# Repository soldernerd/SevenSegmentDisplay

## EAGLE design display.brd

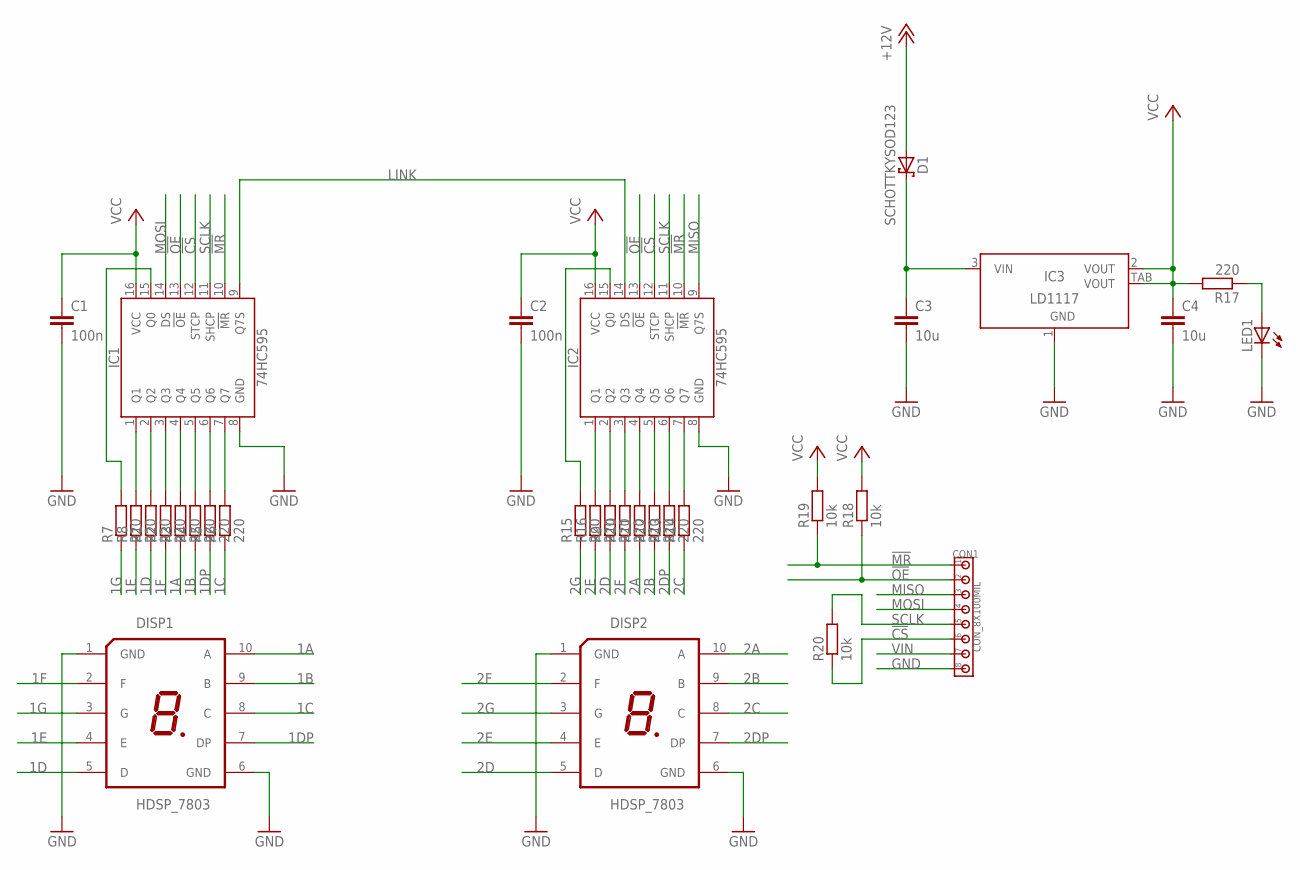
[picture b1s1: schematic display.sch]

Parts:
C1, C2: 100n; C1206
C3, C4: 10u; C1206
CON1: CON_8X100MIL; 100MIL_8X
D1: SCHOTTKYSOD123; SOD123
DISP1, DISP2: HDSP_7803; HDSP-A
IC1, IC2: 74HC595; SO16
IC3: LD1117; SOT223
LED1: LED1206
R1, R2, R3, R4, R5, R6, R7, R8, R9, R10, R11, R12, R13, R14, R15, R16, R17: 220; R1206
R18, R19, R20: 10k; R1206

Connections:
1A: DISP1.10 (A), R3.1
1B: DISP1.9 (B), R4.1
1C: DISP1.8 (C), R6.1
1D: DISP1.5 (D), R1.1
1DP: DISP1.7 (DP), R5.1
1E: DISP1.4 (E), R8.1
1F: DISP1.2 (F), R2.1
1G: DISP1.3 (G), R7.1
2A: DISP2.10 (A), R11.1
2B: DISP2.9 (B), R12.1
2C: DISP2.8 (C), R14.1
2D: DISP2.5 (D), R9.1
2DP: DISP2.7 (DP), R13.1
2E: DISP2.4 (E), R16.1
2F: DISP2.2 (F), R10.1
2G: DISP2.3 (G), R15.1
!CS!: CON1.6, IC1.12 (STCP), IC2.12 (STCP), R20.1
!MR!: CON1.1, IC1.10 (!MR!), IC2.10 (!MR!), R19.1
!OE!: CON1.2, IC1.13 (!OE!), IC2.13 (!OE!), R18.1
GND: C1.2, C2.2, C3.2, C4.2, CON1.8, DISP1.1 (GND), DISP1.6 (GND), DISP2.1 (GND), DISP2.6 (GND), IC1.8 (GND), IC2.8 (GND), IC3.1 (GND), LED1.C
LINK: IC1.9 (Q7S), IC2.14 (DS)
MISO: CON1.3, IC2.9 (Q7S)
MOSI: CON1.4, IC1.14 (DS)
unnamed: IC1.15 (Q0), R7.2
unnamed: IC1.7 (Q7), R6.2
unnamed: IC1.6 (Q6), R5.2
unnamed: IC1.5 (Q5), R4.2
unnamed: IC1.4 (Q4), R3.2
unnamed: IC1.3 (Q3), R2.2
unnamed: IC1.2 (Q2), R1.2
unnamed: IC1.1 (Q1), R8.2
unnamed: IC2.15 (Q0), R15.2
unnamed: IC2.7 (Q7), R14.2
unnamed: IC2.6 (Q6), R13.2
unnamed: IC2.5 (Q5), R12.2
unnamed: IC2.4 (Q4), R11.2
unnamed: IC2.3 (Q3), R10.2
unnamed: IC2.2 (Q2), R9.2
unnamed: IC2.1 (Q1), R16.2
unnamed: C3.1, D1.C, IC3.3 (VIN)
unnamed: LED1.A, R17.1
SCLK: CON1.5, IC1.11 (SHCP), IC2.11 (SHCP), R20.2
VCC: C1.1, C2.1, C4.1, IC1.16 (VCC), IC2.16 (VCC), IC3.2 (VOUT), IC3.TAB (VOUT), R17.2, R18.2, R19.2
VIN: CON1.7, D1.A

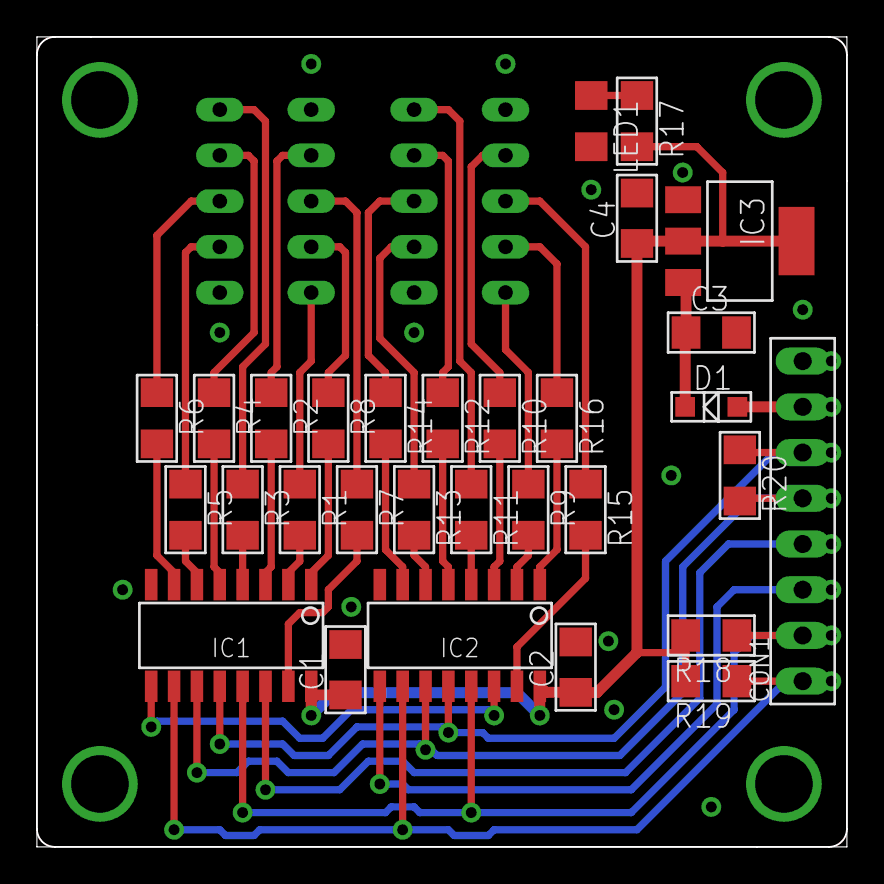
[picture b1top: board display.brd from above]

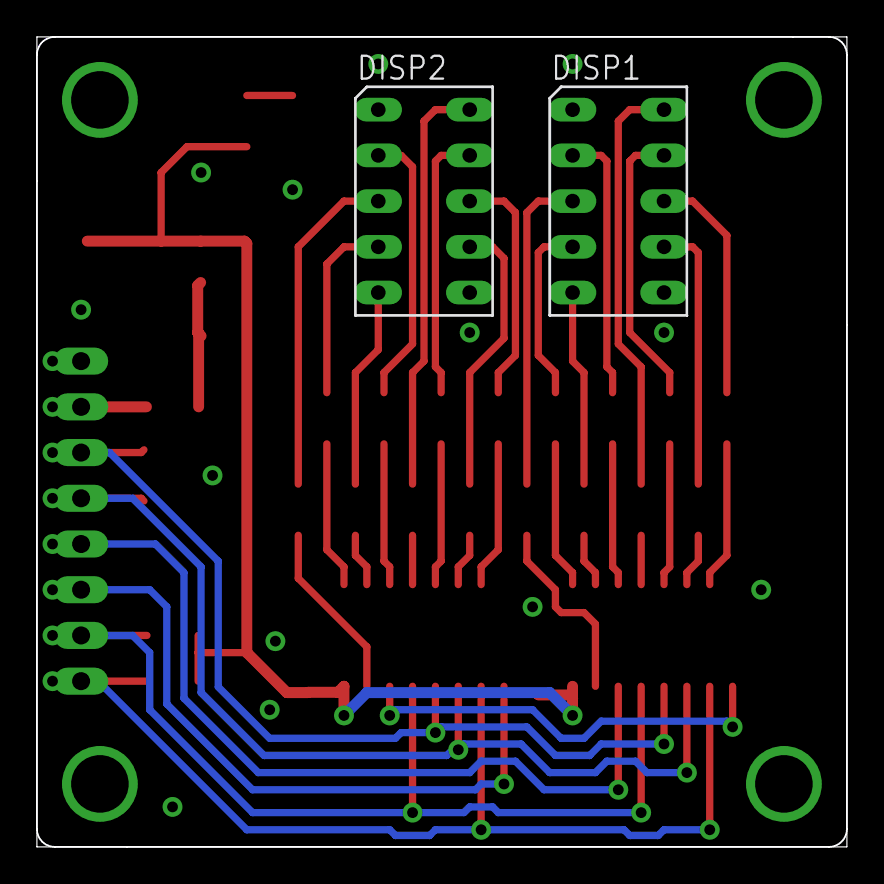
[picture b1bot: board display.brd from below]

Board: 2 copper layers, 45.0 x 45.0 mm, 32 parts (2 on the bottom side), 44 nets.
